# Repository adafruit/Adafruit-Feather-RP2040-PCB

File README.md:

# Adafruit-Feather-RP2040-PCB

Open source PCB files for Feather RP2040

PCB format is EagleCAD schematic and board layout

For more details, check out the product pages at

   * https://www.adafruit.com/products/4884

**We are releasing these files so folks can start creating custom designs based on the RP2040 chip. This design has been built and tested successfully**

Adafruit invests time and resources providing this open source design, 
please support Adafruit and open-source hardware by purchasing 
products from Adafruit!

Designed by Adafruit Industries.  
Creative Commons Attribution, Share-Alike license, check license.txt for more information
All text above must be included in any redistribution

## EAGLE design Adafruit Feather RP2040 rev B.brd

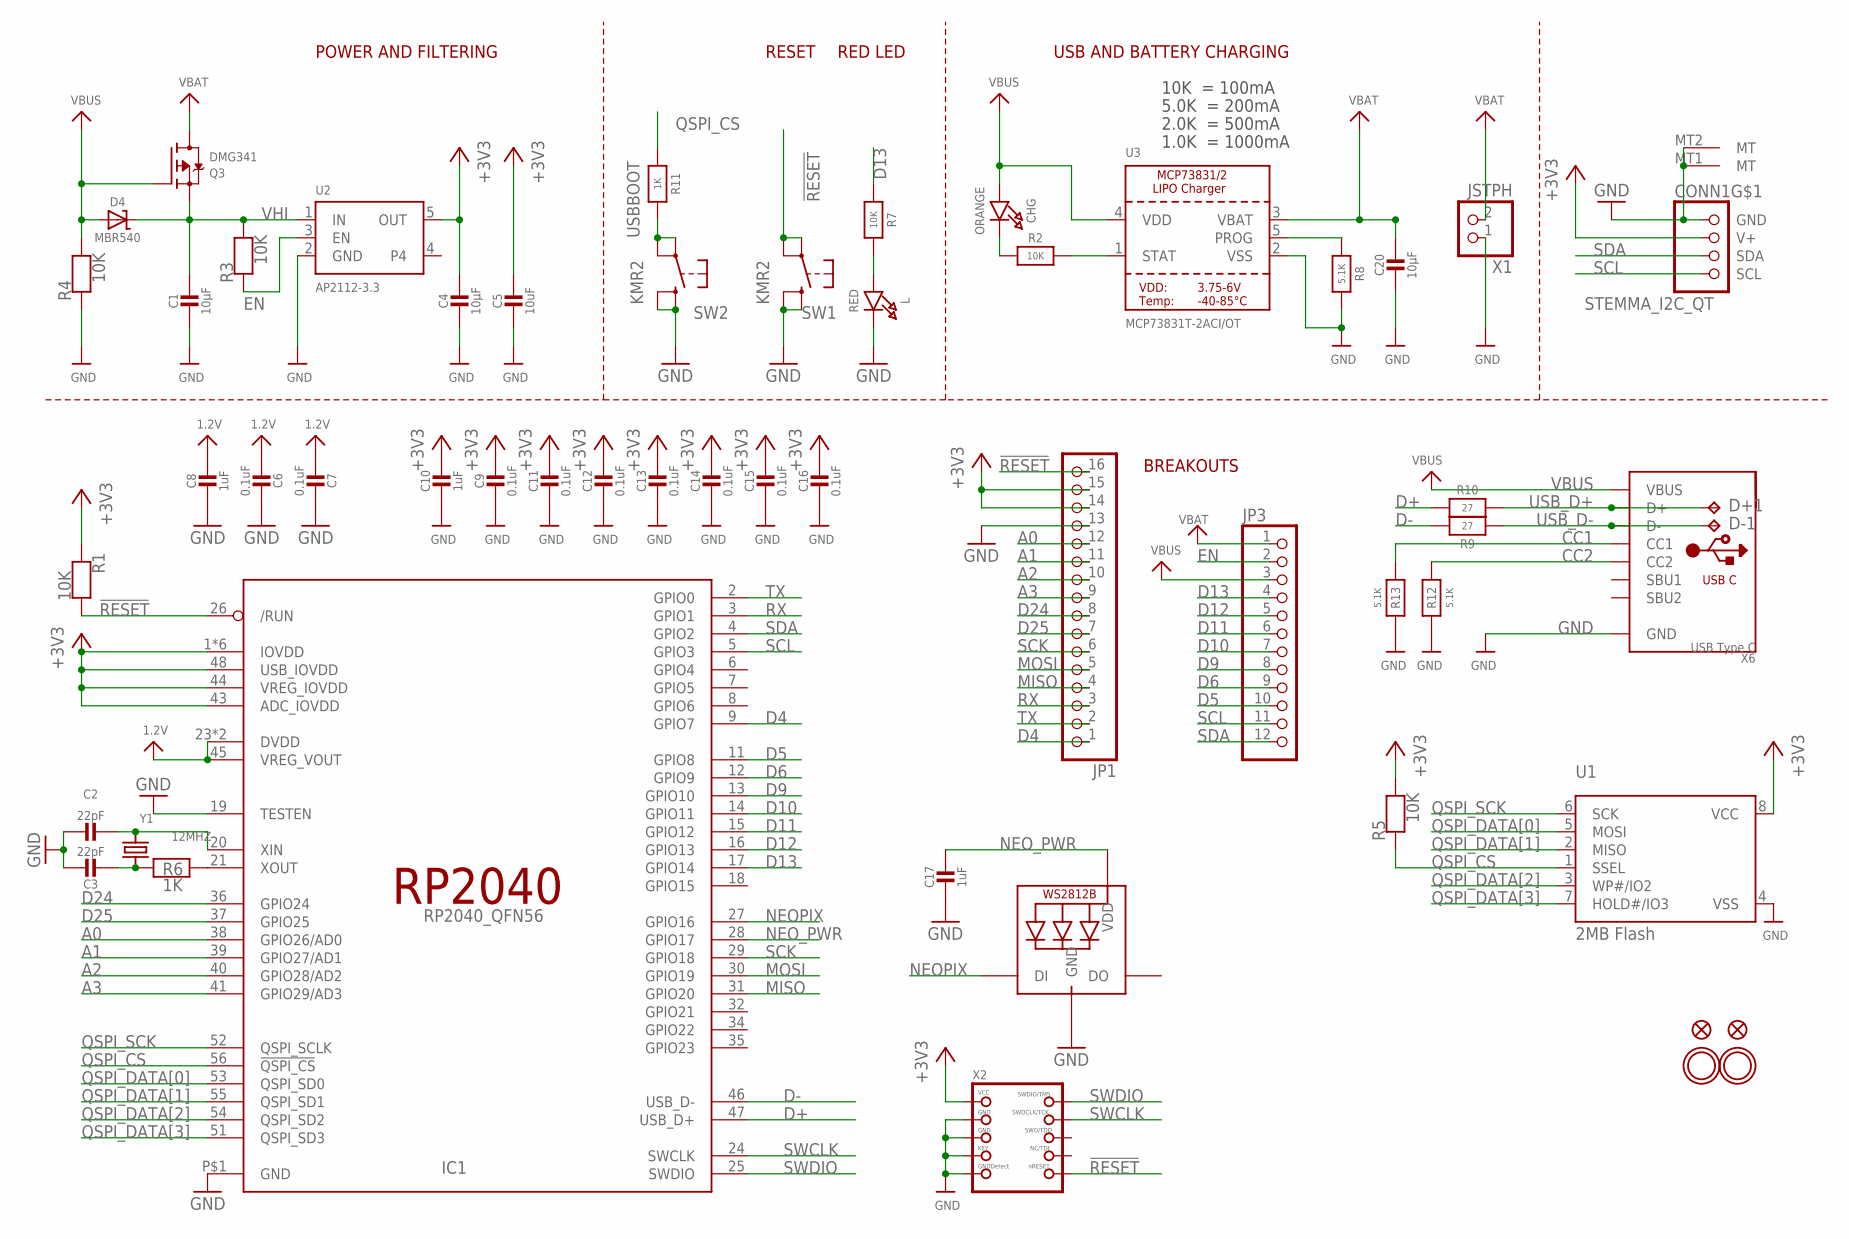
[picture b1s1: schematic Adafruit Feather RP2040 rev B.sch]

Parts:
C1, C4, C20: 10µF; 0805-NO
C2, C3: 22pF; 0603-NO
C5: 10uF; 0805-NO
C6, C7, C9, C11, C12, C13, C14, C15, C16: 0.1uF; 0603-NO
C8, C10, C17: 1uF; 0603-NO
CHG: ORANGE; CHIPLED_0603_NOOUTLINE
CONN1: STEMMA_I2C_QT; JST_SH4
D4: MBR540; SOD-123
D+1: TPB1,27; B1,27
D-1: TPB1,27; B1,27
IC1: RP2040_QFN56; QFN56_7MM_REDUCEDEPAD
JP1: HEADER-1X16ROUND; 1X16_ROUND
JP3: HEADER-1X12; 1X12_ROUND
L: RED; CHIPLED_0603_NOOUTLINE
LED1: WS2812B3535; LED3535
Q3: DMG341; SOT23-R
R1, R2, R3, R4, R5, R7: 10K; 0603-NO
R6, R11: 1K; 0603-NO
R8, R12, R13: 5.1K; 0603-NO
R9, R10: 27; 0603-NO
SW1, SW2: KMR2; BTN_KMR2_4.6X2.8
U1: 2MB Flash; SOIC8_208MIL
U2: AP2112-3.3; SOT23-5@1
U3: MCP73831T-2ACI/OT; SOT23-5
U$31, U$32: MOUNTINGHOLE2.5; MOUNTINGHOLE_2.5_PLATED
U$34, U$35: FIDUCIAL_1MM
X1: JSTPH; JSTPH2_BATT
X2: JTAG-CORTEXBOXPOSTS; 2X05_1.27MM_BOX_POSTS
X6: USB Type C; USB_C_CUSB31-CFM2AX-01-X
Y1: 12MHZ; CRYSTAL_2.5X2

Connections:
1.2V: C6.2, C7.2, C8.1, IC1.23 (DVDD), IC1.45 (VREG_VOUT), IC1.50 (DVDD)
!RESET: IC1.26 (/RUN), JP1.16, R1.2, SW1.A, SW1.A' (P1), X2.10 (NRESET)
+3V3: C4.1, C5.1, C9.1, C10.1, C11.1, C12.1, C13.1, C14.1, C15.1, C16.1, CONN1.2 (V+), IC1.1 (IOVDD), IC1.10 (IOVDD), IC1.22 (IOVDD), IC1.33 (IOVDD), IC1.42 (IOVDD), IC1.43 (ADC_IOVDD), IC1.44 (VREG_IOVDD), IC1.48 (USB_IOVDD), IC1.49 (IOVDD), JP1.14, JP1.15, R1.1, R5.2, U1.8 (VCC), U2.5 (OUT), X2.1 (VCC)
A0: IC1.38 (GPIO26/AD0), JP1.12
A1: IC1.39 (GPIO27/AD1), JP1.11
A2: IC1.40 (GPIO28/AD2), JP1.10
A3: IC1.41 (GPIO29/AD3), JP1.9
CC1: R13.2, X6.A5 (CC1)
CC2: R12.2, X6.B5 (CC2)
D4: IC1.9 (GPIO7), JP1.1
D5: IC1.11 (GPIO8), JP3.10
D6: IC1.12 (GPIO9), JP3.9
D9: IC1.13 (GPIO10), JP3.8
D10: IC1.14 (GPIO11), JP3.7
D11: IC1.15 (GPIO12), JP3.6
D12: IC1.16 (GPIO13), JP3.5
D13: IC1.17 (GPIO14), JP3.4, R7.1
D24: IC1.36 (GPIO24), JP1.8
D25: IC1.37 (GPIO25), JP1.7
D+: IC1.47 (USB_D+), R10.2
D-: IC1.46 (USB_D-), R9.2
EN: JP3.2, R3.1, U2.3 (EN)
GND: C1.2, C2.1, C3.1, C4.2, C5.2, C6.1, C7.1, C8.2, C9.2, C10.2, C11.2, C12.2, C13.2, C14.2, C15.2, C16.2, C17.2, C20.2, CONN1.1 (GND), CONN1.MT1 (MT), CONN1.MT2 (MT), IC1.19 (TESTEN), IC1.P$1 (GND), JP1.13, L.C, LED1.4 (GND), R4.1, R8.2, R12.1, R13.1, SW1.B (S), SW1.B' (S1), SW2.B (S), SW2.B' (S1), U1.4 (VSS), U2.2 (GND), U3.2 (VSS), X1.1, X2.3 (GND), X2.5 (GND), X2.7 (KEY), X2.9 (GNDDETECT), X6.A1B12 (GND), X6.B1A12 (GND)
MISO: IC1.31 (GPIO20), JP1.4
MOSI: IC1.30 (GPIO19), JP1.5
unnamed: CHG.C, R2.1
unnamed: L.A, R7.2
unnamed: R2.2, U3.1 (STAT)
unnamed: R8.1, U3.5 (PROG)
unnamed: C2.2, IC1.20 (XIN), Y1.3 (2)
unnamed: C3.2, R6.1, Y1.1
unnamed: IC1.21 (XOUT), R6.2
NEOPIX: IC1.27 (GPIO16), LED1.1 (DI)
NEO_PWR: C17.1, IC1.28 (GPIO17), LED1.2 (VDD)
QSPI_CS: IC1.56 (!QSPI_CS), R5.1, R11.1, U1.1 (SSEL)
QSPI_DATA[0]: IC1.53 (QSPI_SD0), U1.5 (MOSI)
QSPI_DATA[1]: IC1.55 (QSPI_SD1), U1.2 (MISO)
QSPI_DATA[2]: IC1.54 (QSPI_SD2), U1.3 (WP#/IO2)
QSPI_DATA[3]: IC1.51 (QSPI_SD3), U1.7 (HOLD#/IO3)
QSPI_SCK: IC1.52 (QSPI_SCLK), U1.6 (SCK)
RX: IC1.3 (GPIO1), JP1.3
SCK: IC1.29 (GPIO18), JP1.6
SCL: CONN1.4 (SCL), IC1.5 (GPIO3), JP3.11
SDA: CONN1.3 (SDA), IC1.4 (GPIO2), JP3.12
SWCLK: IC1.24 (SWCLK), X2.4 (SWDCLK)
SWDIO: IC1.25 (SWDIO), X2.2 (SWDIO)
TX: IC1.2 (GPIO0), JP1.2
USBBOOT: R11.2, SW2.A, SW2.A' (P1)
USB_D+: D+1.TP, R10.1, X6.A6 (D+), X6.B6 (D+)
USB_D-: D-1.TP, R9.1, X6.A7 (D-), X6.B7 (D-)
VBAT: C20.1, JP3.1, Q3.3 (D), U3.3 (VBAT), X1.2
VBUS: CHG.A, D4.A, JP3.3, Q3.1 (G), R4.2, U3.4 (VDD), X6.A4B9 (VBUS), X6.B4A9 (VBUS)
VHI: C1.1, D4.C, Q3.2 (S), R3.2, U2.1 (IN)

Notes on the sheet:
POWER AND FILTERING
RESET
10K = 100mA
5.0K = 200mA
2.0K = 500mA
1.0K = 1000mA
USB AND BATTERY CHARGING
BREAKOUTS
RED LED

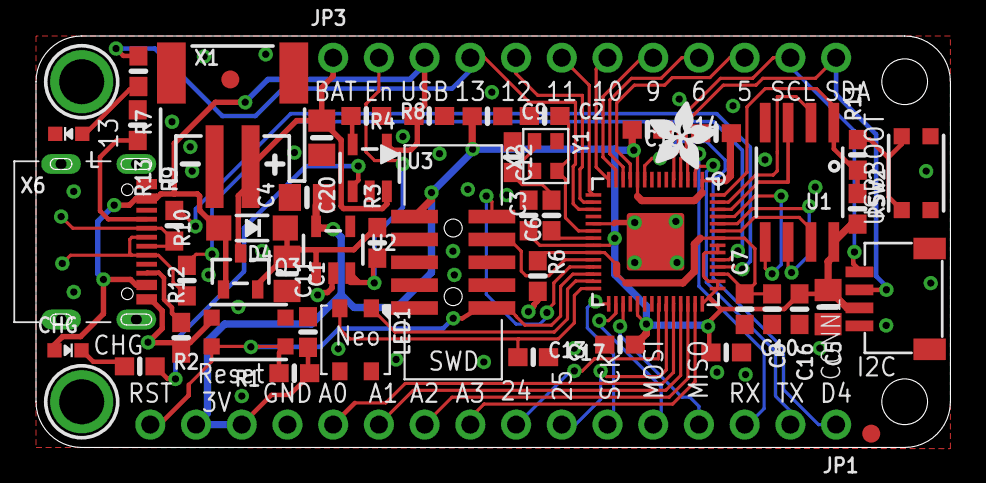
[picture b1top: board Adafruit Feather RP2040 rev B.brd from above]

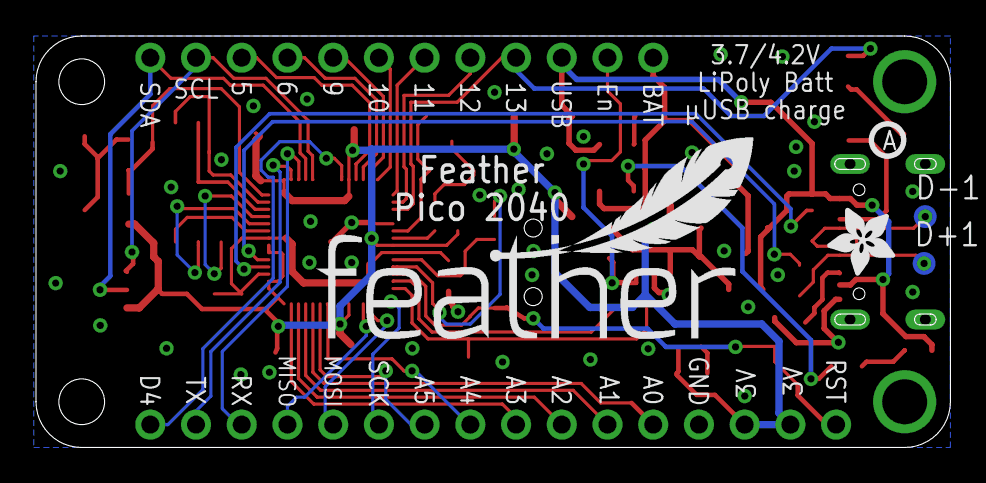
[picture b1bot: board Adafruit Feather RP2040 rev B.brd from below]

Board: 2 copper layers, 50.8 x 22.9 mm, 59 parts (5 on the bottom side), 53 nets.

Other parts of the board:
U$9: FEATHERLOGO
U$12, U$28: ADAFRUIT_3.5MM
U$13: PCBFEAT-REV-040

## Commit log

2021-01-21 init
2021-01-21 flippy
2021-03-03 Add board files
2021-03-23 add test program
2021-05-07 Adding pinout image file.
2021-12-10 Add PrettyPins PDF
2022-12-02 Add new rev.

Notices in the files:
parts and their libraries:
microbuilder: This work is placed in the public domain, and may be freely used for commercial and non-commercial work with the following conditions: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
